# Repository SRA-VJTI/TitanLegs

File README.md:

# TitanLegs

## Schematics

## PCB Design
### Front Side

### Back Side

### Routing

## TASKS

- [ ] Simulation
  - [ ] Plain Terrain
  - [ ] Rough Terrain
- [ ] Design Actuators
  - [ ] SolidWorks Designing
  - [ ] 3D printing of Legs
  - [ ] Assembling the parts
- [ ] Schematics 
- [ ] Firmware
  - [ ] Actuator
  - [ ] Complete Quadruped

## RESOURCES
* [3D Printed Robot Actuator(hackaday project)](https://hackaday.io/project/157812-3d-printed-robot-actuator)
* [GoGo RC Motor(used in above hackaday project)](https://gogo-rc.com/store/index.php?route=product/product&product_id=3493&search=5010)
* [BLDC Motor Algorithm](https://www.renesas.com/us/en/application/home-building/motor-control-solutions/motor-algorithms/bldc)
* [Python Dynamics Simulation-Part 1](https://medium.com/robotics-devs/python-dynamics-simulations-part-1-f89648a35561)
* [Python BLDC Simulator](https://github.com/gtoonstra/bldc-sim)
* [Gait Analysis of Quadruped](https://cjme.springeropen.com/articles/10.1186/s10033-019-0321-2)
* [Brushless Actuator(Arduino Compatible)](https://hackaday.io/project/165217-brushless-actuator-arduino-compatible)
* [ESP-32 BLDC Robot Actuator Controller](https://hackaday.io/project/169905-esp-32-bldc-robot-actuator-controller)
* [Open Source Motor Control - Odrive](https://odriverobotics.com/)
* [Dynamixel- All in one smart Actuator System](https://www.robotis.us/dynamixel/)
* [Quadruped Simulation on Vrep](http://galvanicloop.com/blog/post/7/quadruped-robot-5-simulation-on-v-rep)
* [Quadruped Robots URDF and Simulation tools](https://github.com/chvmp/champ)
* [Fusion 360 script to export URDF](https://github.com/syuntoku14/fusion2urdf)
* [Another Fusion 360 script to export urdf files](https://github.com/yanshil/Fusion2PyBullet)
* [Onshape- browser based CAD tool](https://onshape-to-robot.readthedocs.io/en/latest/design.html)

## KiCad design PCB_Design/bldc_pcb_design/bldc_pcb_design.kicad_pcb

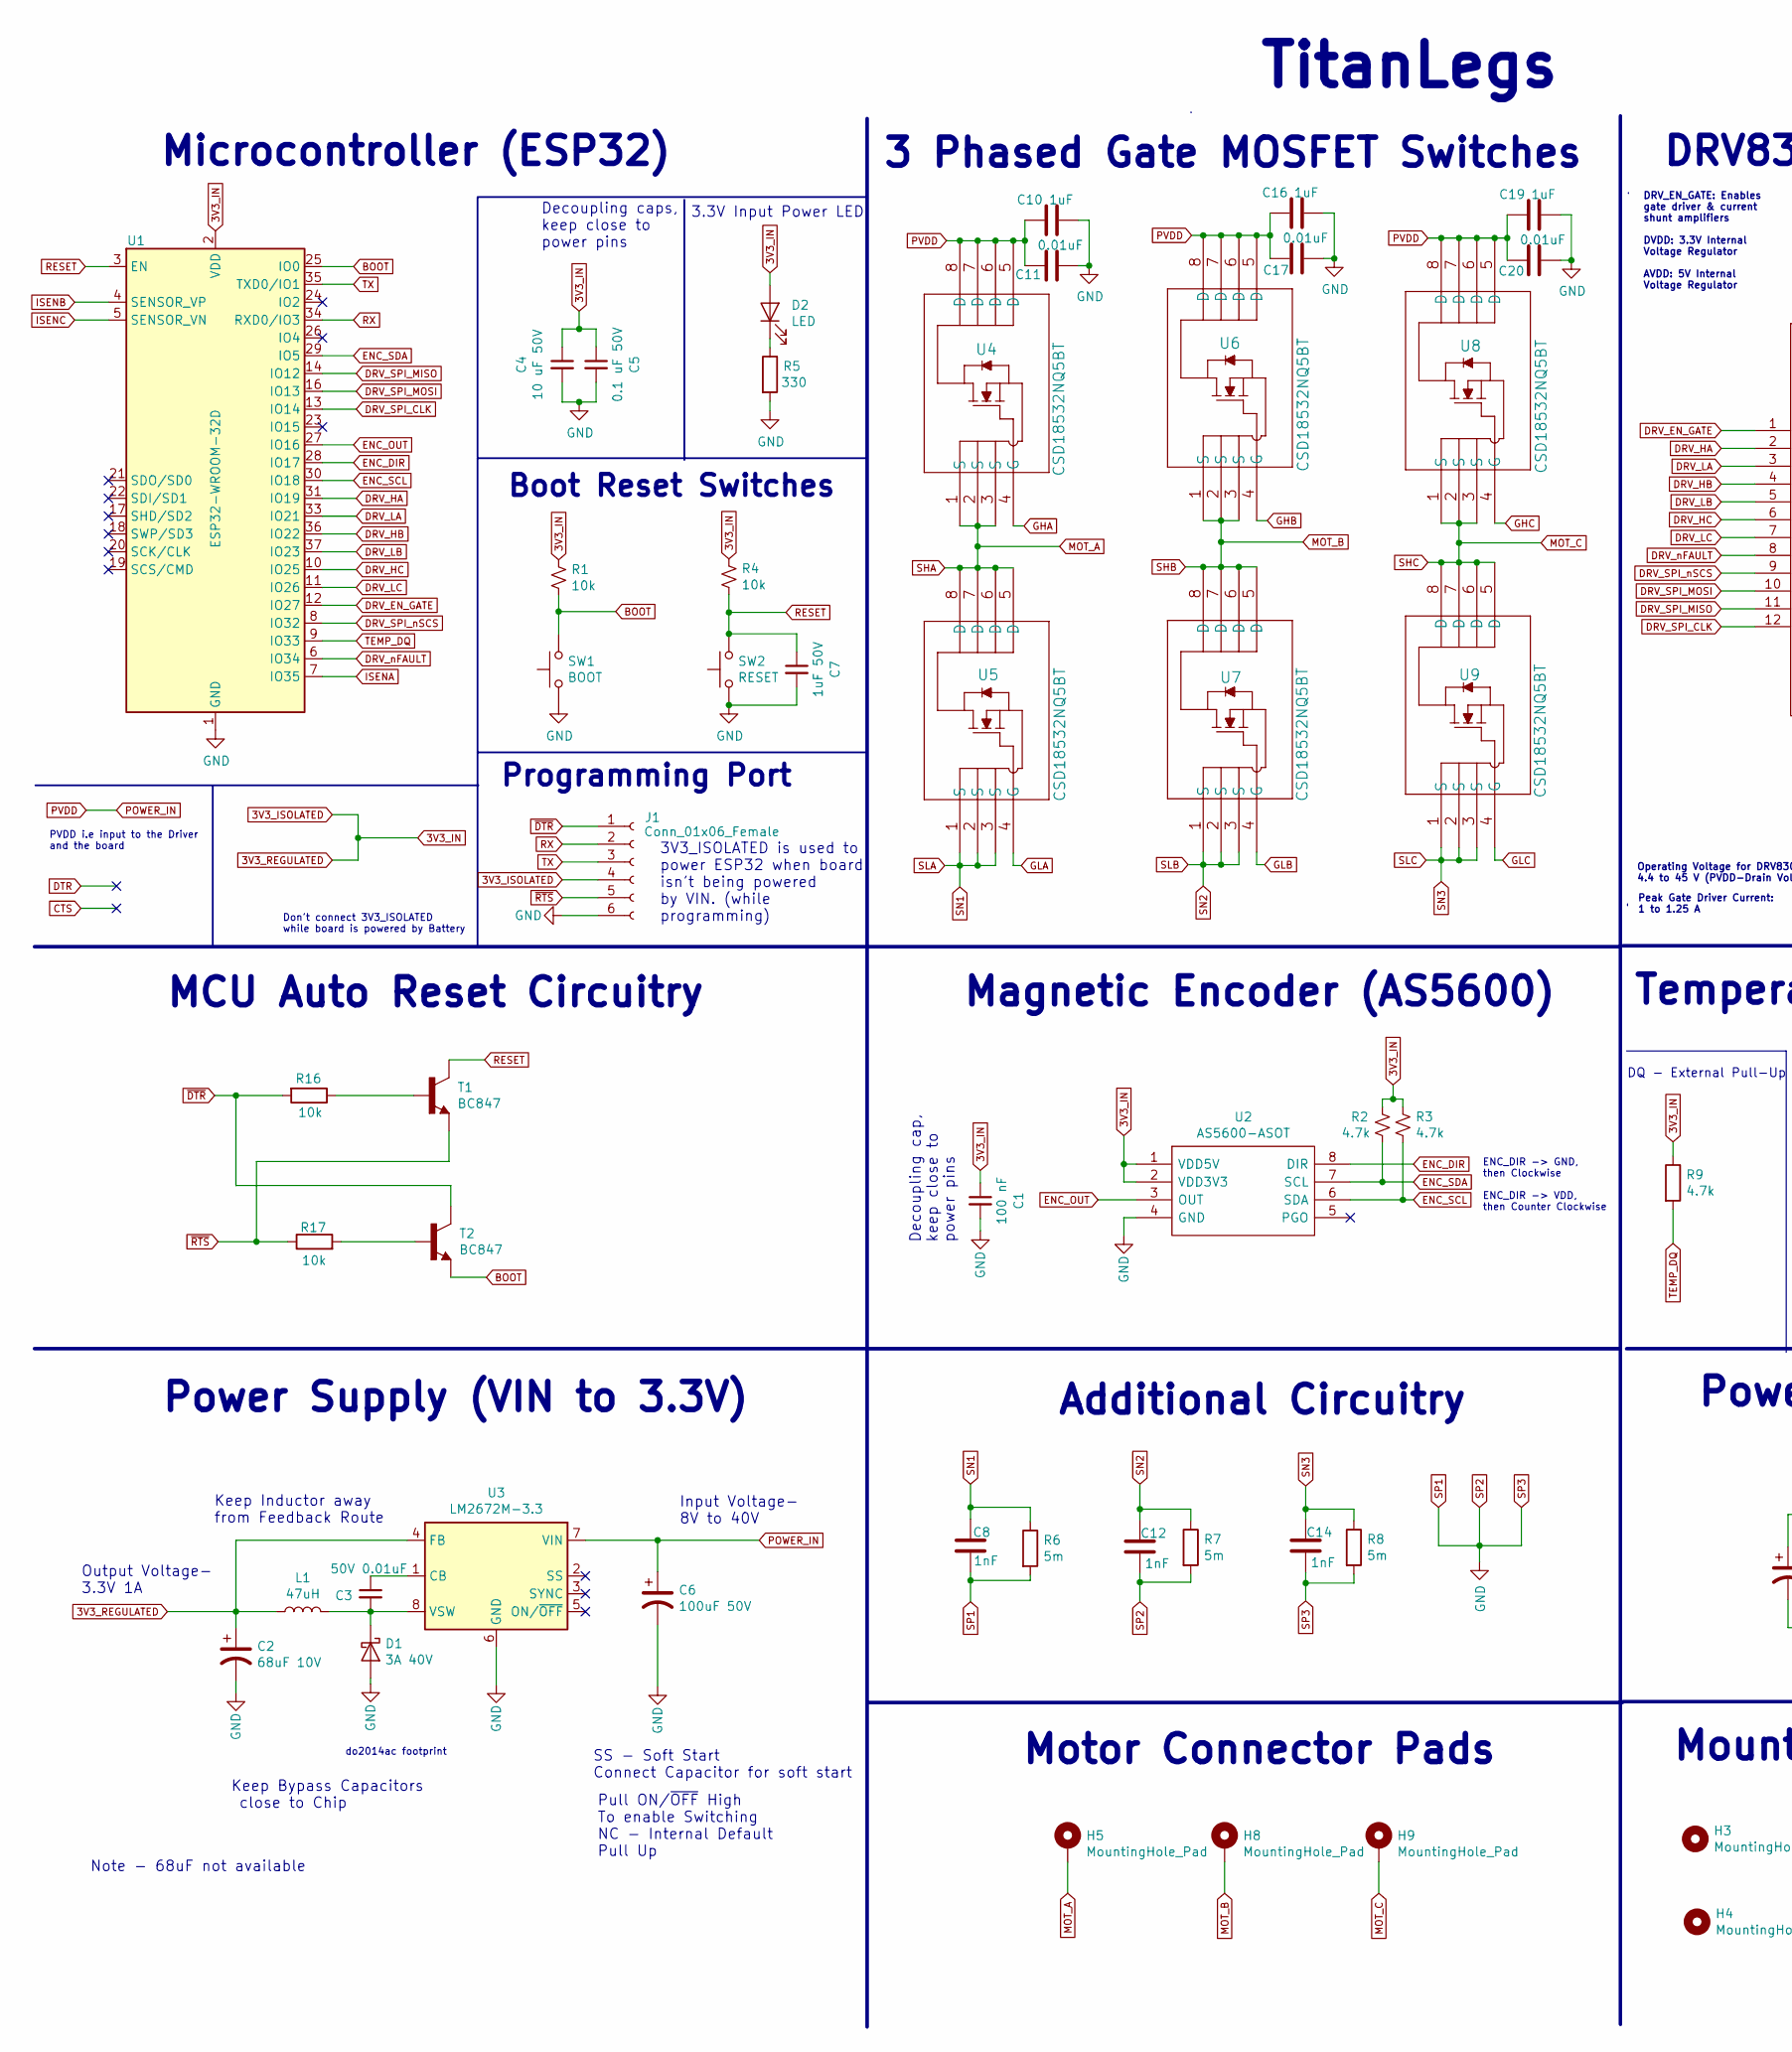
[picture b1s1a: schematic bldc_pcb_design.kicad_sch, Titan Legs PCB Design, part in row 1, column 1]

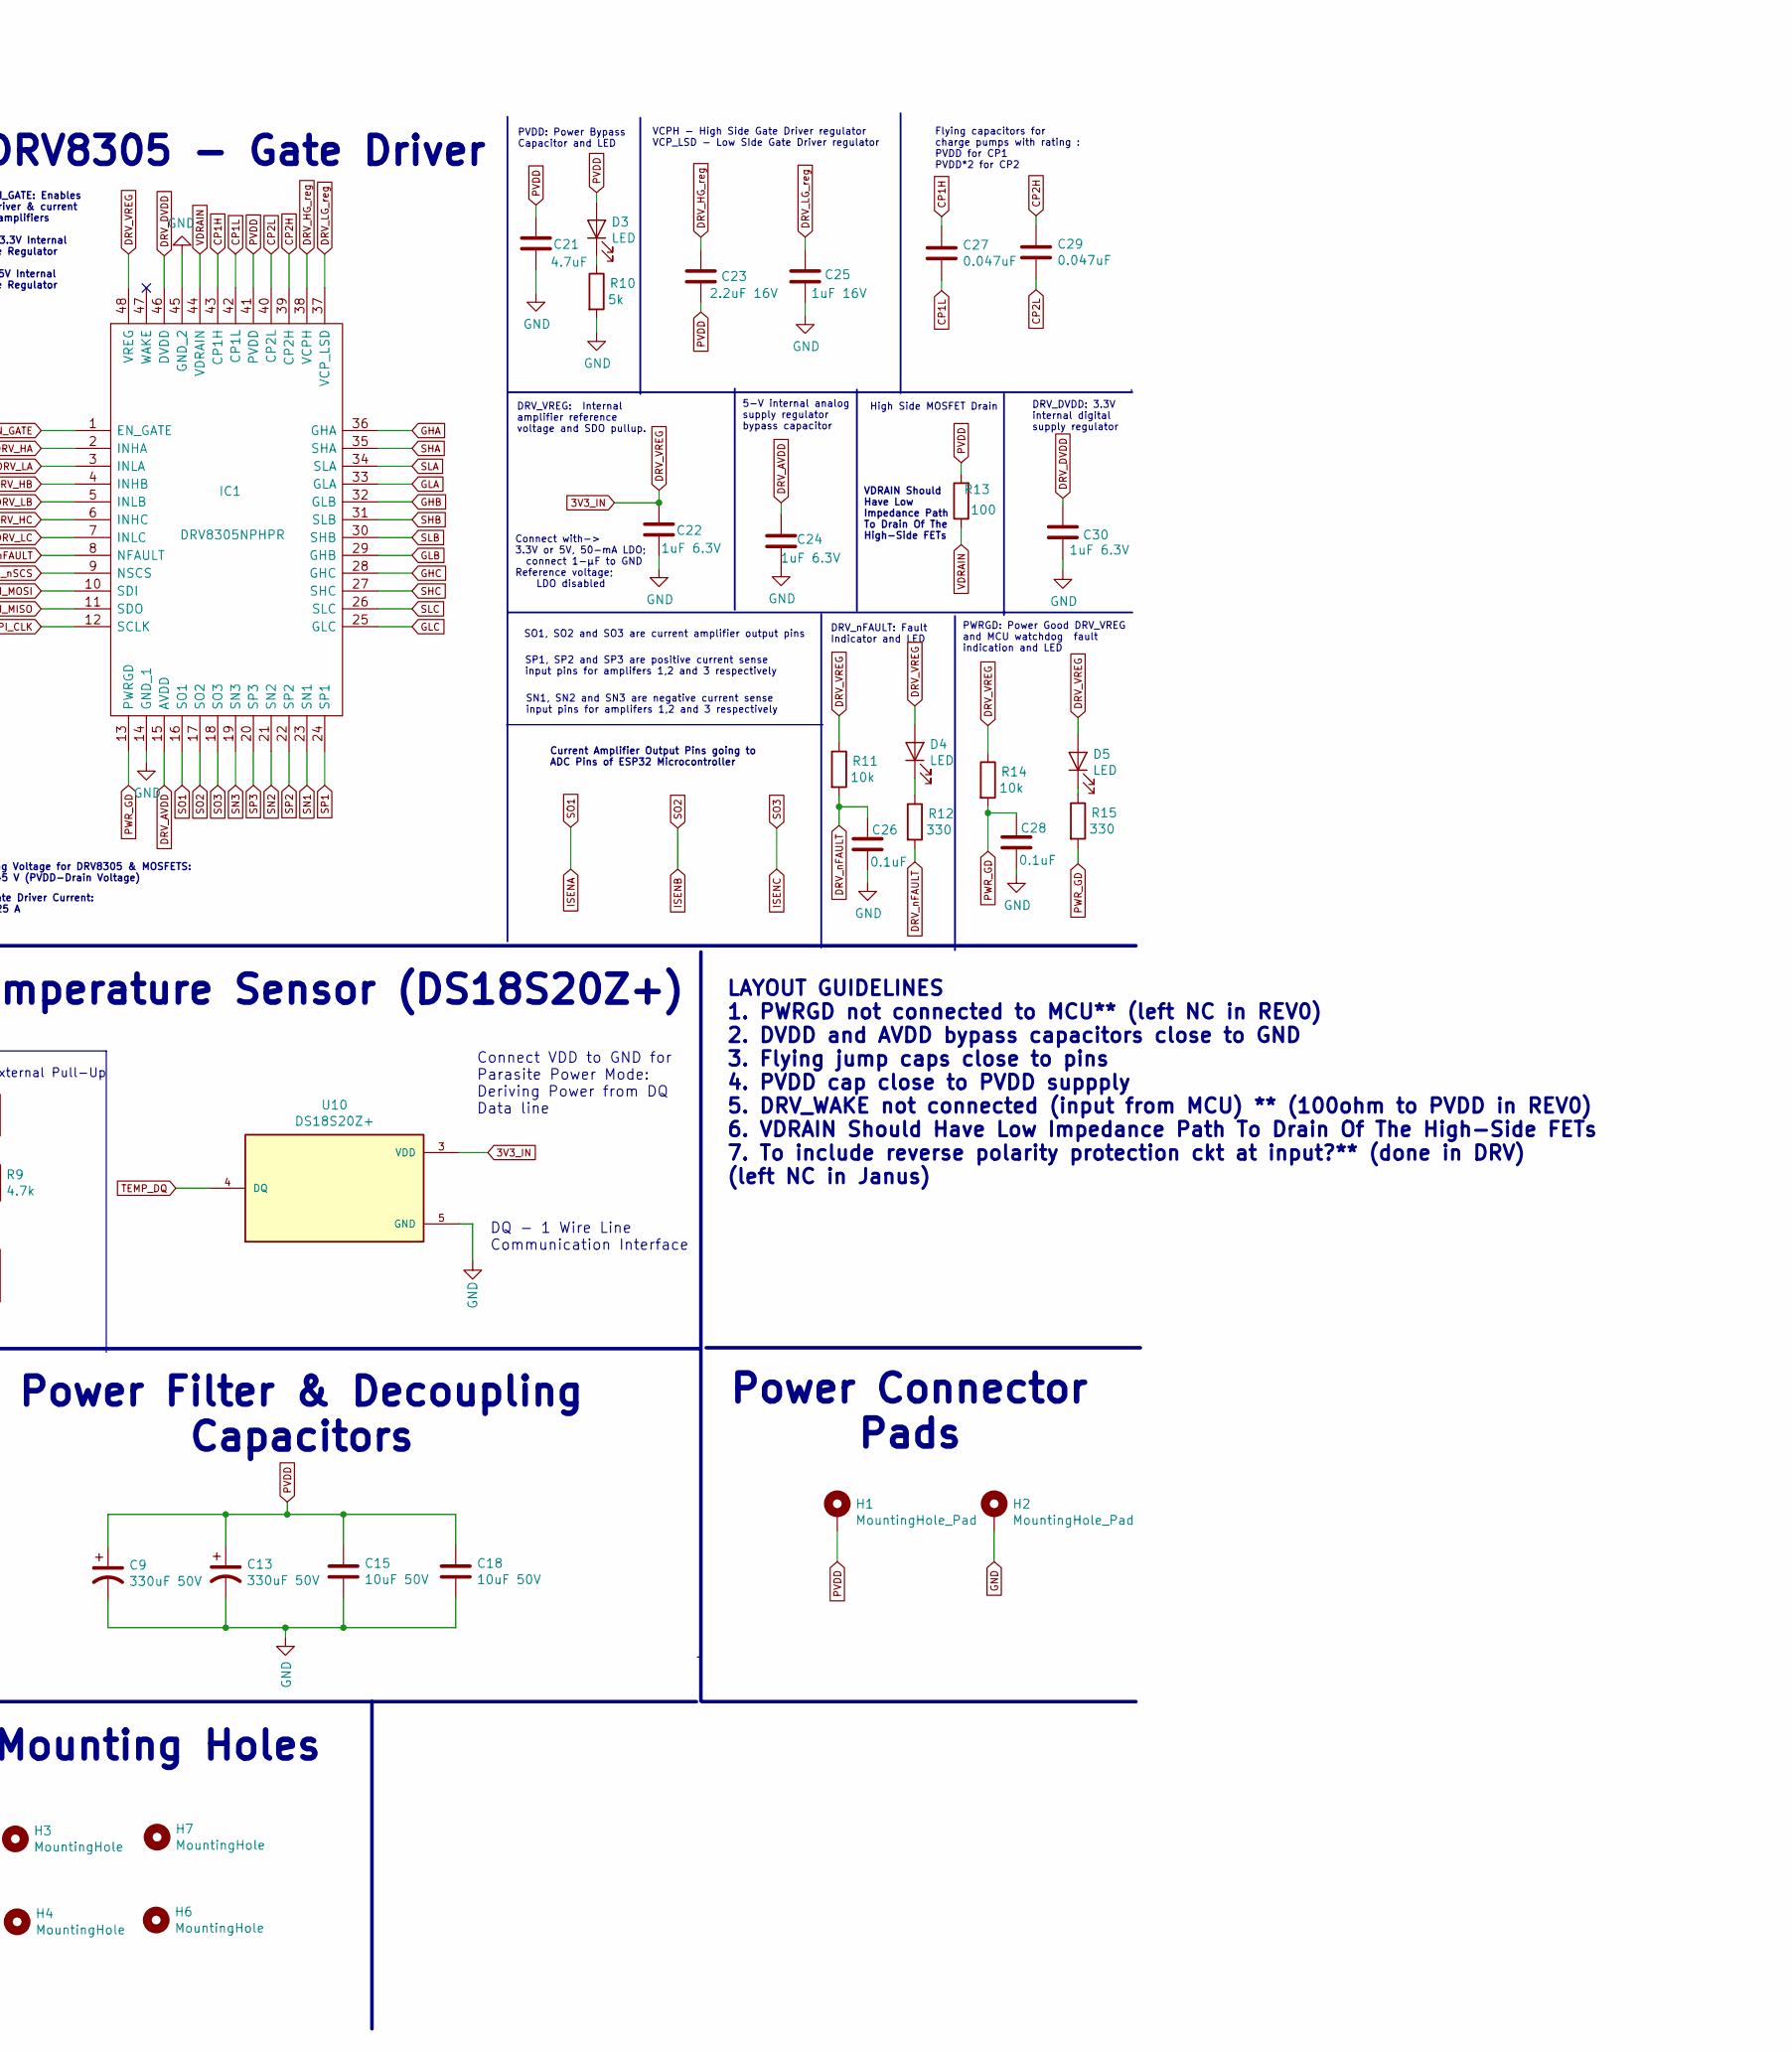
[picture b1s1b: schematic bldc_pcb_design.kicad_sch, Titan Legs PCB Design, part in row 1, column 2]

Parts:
C1: 100 nF; C_0603_1608Metric
C2: 68uF 10V; CP_Elec_6.3x7.7
C3: 50V 0.01uF; C_0603_1608Metric
C4: 10 uF 50V; C_0603_1608Metric
C5: 0.1 uF 50V; C_0603_1608Metric
C6: 100uF 50V; CP_Elec_6.3x7.7
C7: 1uF 50V; C_0603_1608Metric
C8, C12, C14: 1nF; C_0603_1608Metric
C9, C13: 330uF 50V; CP_Elec_10x10
C10, C16, C19: 1uF; C_0603_1608Metric
C11, C17, C20: 0.01uF; C_0603_1608Metric
C15, C18: 10uF 50V; C_0603_1608Metric
C21: 4.7uF; C_0603_1608Metric
C22, C24, C30: 1uF 6.3V; C_0603_1608Metric
C23: 2.2uF 16V; C_0603_1608Metric
C25: 1uF 16V; C_0603_1608Metric
C26, C28: 0.1uF; C_0603_1608Metric
C27, C29: 0.047uF; C_0603_1608Metric
D1: 3A 40V; D_0603_1608Metric
D2, D3, D4, D5: LED; D_0603_1608Metric
H1, H2: MountingHole_Pad; MountingHole_6.4mm_M6_DIN965_Pad
H3, H4, H6, H7: MountingHole; MountingHole_3.2mm_M3
H5, H8, H9: MountingHole_Pad; MountingHole_2.2mm_M2_DIN965_Pad
IC1: DRV8305NPHPR; DRV8305NEPHPRQ1_with_GND_pads; Manufacturer_Part_Number DRV8305NPHPR; Mouser Part Number 595-DRV8305NPHPR
J1: Conn_01x06_Female; PinHeader_1x06_P2.54mm_Vertical
L1: 47uH; 8D43
R1, R4, R11, R14, R16, R17: 10k; R_0603_1608Metric
R2, R3, R9: 4.7k; R_0603_1608Metric
R5, R12, R15: 330; R_0603_1608Metric
R6, R7, R8: 5m; Shunt_Resistor_L7.0mm_B4.0mm_H1.0mm
R10: 5k; R_0603_1608Metric
R13: 100; R_0603_1608Metric
SW1: BOOT; Tactile_Switch
SW2: RESET; Tactile_Switch
T1, T2: BC847
U1: ESP32-WROOM-32D; ESP32-WROOM-32
U2: AS5600-ASOT; AS5600; Manufacturer_Part_Number AS5600-ASOT; Mouser Part Number 985-AS5600-ASOT
U3: LM2672M-3.3; SOIC-8_3.9x4.9mm_P1.27mm
U4, U5, U6, U7, U8, U9: CSD18532NQ5BT; CSD18532NQ5B
U10: DS18S20Z+; DS18S20Z_; PARTREV 3

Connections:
3V3_IN: C1.1, C2.1, C4.1, C5.1, C22.2, D2.2 (A), D4.2 (A), D5.2 (A), IC1.48 (VREG), J1.4, L1.1, R1.1, R2.2, R3.1, R4.1, R9.1, R11.1, R14.1, U1.2 (VDD), U2.1 (VDD5V), U2.2 (VDD3V3), U3.4 (FB), U10.3 (VDD)
BOOT: R1.2, SW1.2, T2.2, U1.25 (IO0)
CP1H: C27.1, IC1.43 (CP1H)
CP1L: C27.2, IC1.42 (CP1L)
CP2H: C29.1, IC1.39 (CP2H)
CP2L: C29.2, IC1.40 (CP2L)
DRV_AVDD: C24.2, IC1.15 (AVDD)
DRV_DVDD: C30.2, IC1.46 (DVDD)
DRV_EN_GATE: IC1.1 (EN_GATE), U1.12 (IO27)
DRV_HA: IC1.2 (INHA), U1.31 (IO19)
DRV_HB: IC1.4 (INHB), U1.36 (IO22)
DRV_HC: IC1.6 (INHC), U1.10 (IO25)
DRV_HG_reg: C23.1, IC1.38 (VCPH)
DRV_LA: IC1.3 (INLA), U1.33 (IO21)
DRV_LB: IC1.5 (INLB), U1.37 (IO23)
DRV_LC: IC1.7 (INLC), U1.11 (IO26)
DRV_LG_reg: C25.1, IC1.37 (VCP_LSD)
DRV_SPI_CLK: IC1.12 (SCLK), U1.13 (IO14)
DRV_SPI_MISO: IC1.11 (SDO), U1.14 (IO12)
DRV_SPI_MOSI: IC1.10 (SDI), U1.16 (IO13)
DRV_SPI_nSCS: IC1.9 (NSCS), U1.8 (IO32)
DRV_nFAULT: C26.1, IC1.8 (NFAULT), R11.2, R12.2, U1.6 (IO34)
ENC_DIR: U1.28 (IO17), U2.8 (DIR)
ENC_OUT: U1.27 (IO16), U2.3 (OUT)
ENC_SCL: R3.2, U1.30 (IO18), U2.6 (SDA)
ENC_SDA: R2.1, U1.29 (IO5), U2.7 (SCL)
GHA: IC1.36 (GHA), U4.4 (G)
GHB: IC1.32 (GLB), U6.4 (G)
GHC: IC1.28 (GHC), U8.4 (G)
GLA: IC1.33 (GLA), U5.4 (G)
GLB: IC1.29 (GHB), U7.4 (G)
GLC: IC1.25 (GLC), U9.4 (G)
GND: C1.2, C2.2, C4.2, C5.2, C6.2, C7.2, C8.2, C9.2, C10.2, C11.2, C12.2, C13.2, C14.2, C15.2, C16.2, C17.2, C18.2, C19.2, C20.2, C21.1, C22.1, C24.1, C25.2, C26.2, C28.2, C30.1, D1.2 (A), H2.1, IC1.14 (GND_1), IC1.20 (SP3), IC1.22 (SP2), IC1.24 (SP1), IC1.45 (GND_2), J1.6, R5.2, R6.2, R7.2, R8.2, R10.2, SW1.1, SW2.1, U1.1 (GND), U1.15 (GND), U1.38 (GND), U1.39 (GND), U2.4 (GND), U3.6 (GND), U10.5 (GND)
ISENA: IC1.16 (SO1), U1.7 (IO35)
ISENB: IC1.17 (SO2), U1.4 (SENSOR_VP)
ISENC: IC1.18 (SO3), U1.5 (SENSOR_VN)
MOT_A: H5.1, IC1.35 (SHA), U4.1 (S), U4.2 (S), U4.3 (S), U5.5 (D), U5.6 (D), U5.7 (D), U5.8 (D)
MOT_B: H8.1, IC1.31 (SLB), U6.1 (S), U6.2 (S), U6.3 (S), U7.5 (D), U7.6 (D), U7.7 (D), U7.8 (D)
MOT_C: H9.1, IC1.27 (SHC), U8.1 (S), U8.2 (S), U8.3 (S), U9.5 (D), U9.6 (D), U9.7 (D), U9.8 (D)
unnamed: C3.1, U3.1 (CB)
unnamed: C3.2, D1.1 (K), L1.2, U3.8 (VSW)
unnamed: D2.1 (K), R5.1
unnamed: D3.1 (K), R10.1
unnamed: D4.1 (K), R12.1
unnamed: D5.1 (K), R15.1
unnamed: R16.1, T1.1
unnamed: R17.2, T2.1
POWER_IN: C6.1, C9.1, C10.1, C11.1, C13.1, C15.1, C16.1, C17.1, C18.1, C19.1, C20.1, C21.2, C23.2, D3.2 (A), H1.1, IC1.41 (PVDD), R13.2, U3.7 (VIN), U4.5 (D), U4.6 (D), U4.7 (D), U4.8 (D), U6.5 (D), U6.6 (D), U6.7 (D), U6.8 (D), U8.5 (D), U8.6 (D), U8.7 (D), U8.8 (D)
PWR_GD: C28.1, IC1.13 (PWRGD), R14.2, R15.2
RESET: C7.1, R4.2, SW2.2, T1.3, U1.3 (EN)
RX: J1.2, U1.34 (RXD0/IO3)
SLA: C8.1, IC1.23 (SN1), IC1.34 (SLA), R6.1, U5.1 (S), U5.2 (S), U5.3 (S)
SLB: C12.1, IC1.21 (SN2), IC1.30 (SHB), R7.1, U7.1 (S), U7.2 (S), U7.3 (S)
SLC: C14.1, IC1.19 (SN3), IC1.26 (SLC), R8.1, U9.1 (S), U9.2 (S), U9.3 (S)
TEMP_DQ: R9.2, U1.9 (IO33), U10.4 (DQ)
TX: J1.3, U1.35 (TXD0/IO1)
VDRAIN: IC1.44 (VDRAIN), R13.1
~DTR: J1.1, R16.2, T2.3
~RTS: J1.5, R17.1, T1.2

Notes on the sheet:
ENC_DIR -> GND, then Clockwise ENC_DIR -> VDD, then Counter Clockwise
Power Connector Pads
Programming Port
DQ - 1 Wire Line Communication Interface
5-V internal analog supply regulator bypass capacitor
Output Voltage- 3.3V 1A
do2014ac footprint
PWRGD: Power Good DRV_VREG and MCU watchdog fault indication and LED
DRV_DVDD: 3.3V internal digital supply regulator
DQ - External Pull-Up
Peak Gate Driver Current: 1 to 1.25 A
LAYOUT GUIDELINES 1. PWRGD not connected to MCU** (left NC in REV0) 2. DVDD and AVDD bypass capacitors close to GND 3. Flying jump caps close to pins 4. PVDD cap close to PVDD suppply 5. DRV_WAKE not connected (input from MCU) ** (100ohm to PVDD in REV0) 6. VDRAIN Should Have Low Impedance Path To 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
Note - 68uF not available
SN1, SN2 and SN3 are negative current sense input pins for amplifers 1,2 and 3 respectively
Operating Voltage for DRV8305 & MOSFETS: 4.4 to 45 V (PVDD-Drain Voltage)
SS - Soft Start Connect Capacitor for soft start
Additional Circuitry
SO1, SO2 and SO3 are current amplifier output pins
Current Amplifier Output Pins going to ADC Pins of ESP32 Microcontroller
Don't connect 3V3_ISOLATED while board is powered by Battery
3V3_ISOLATED is used to power ESP32 when board isn't being powered by VIN. (while programming)
DRV_VREG: Internal amplifier reference voltage and SDO pullup.
High Side MOSFET Drain
Connect VDD to GND for Parasite Power Mode: Deriving Power from DQ Data line
Power Supply (VIN to 3.3V)
Temperature Sensor (DS18S20Z+)
SP1, SP2 and SP3 are positive current sense input pins for amplifers 1,2 and 3 respectively
VDRAIN Should Have Low Impedance Path To Drain Of The High-Side FETs
Boot Reset Switches
DRV_EN_GATE: Enables gate driver & current shunt amplifiers DVDD: 3.3V Internal Voltage Regulator AVDD: 5V Internal Voltage Regulator
DRV_nFAULT: Fault Indicator and LED
Pull ON/~{OFF} High To enable Switching NC - Internal Default Pull Up
Flying capacitors for charge pumps with rating : PVDD for CP1 PVDD*2 for CP2
Microcontroller (ESP32)
Keep Bypass Capacitors close to Chip
Mounting Holes
PVDD i.e input to the Driver and the board
TitanLegs
Decoupling cap, keep close to power pins
VCPH - High Side Gate Driver regulator VCP_LSD - Low SIde Gate Driver regulator

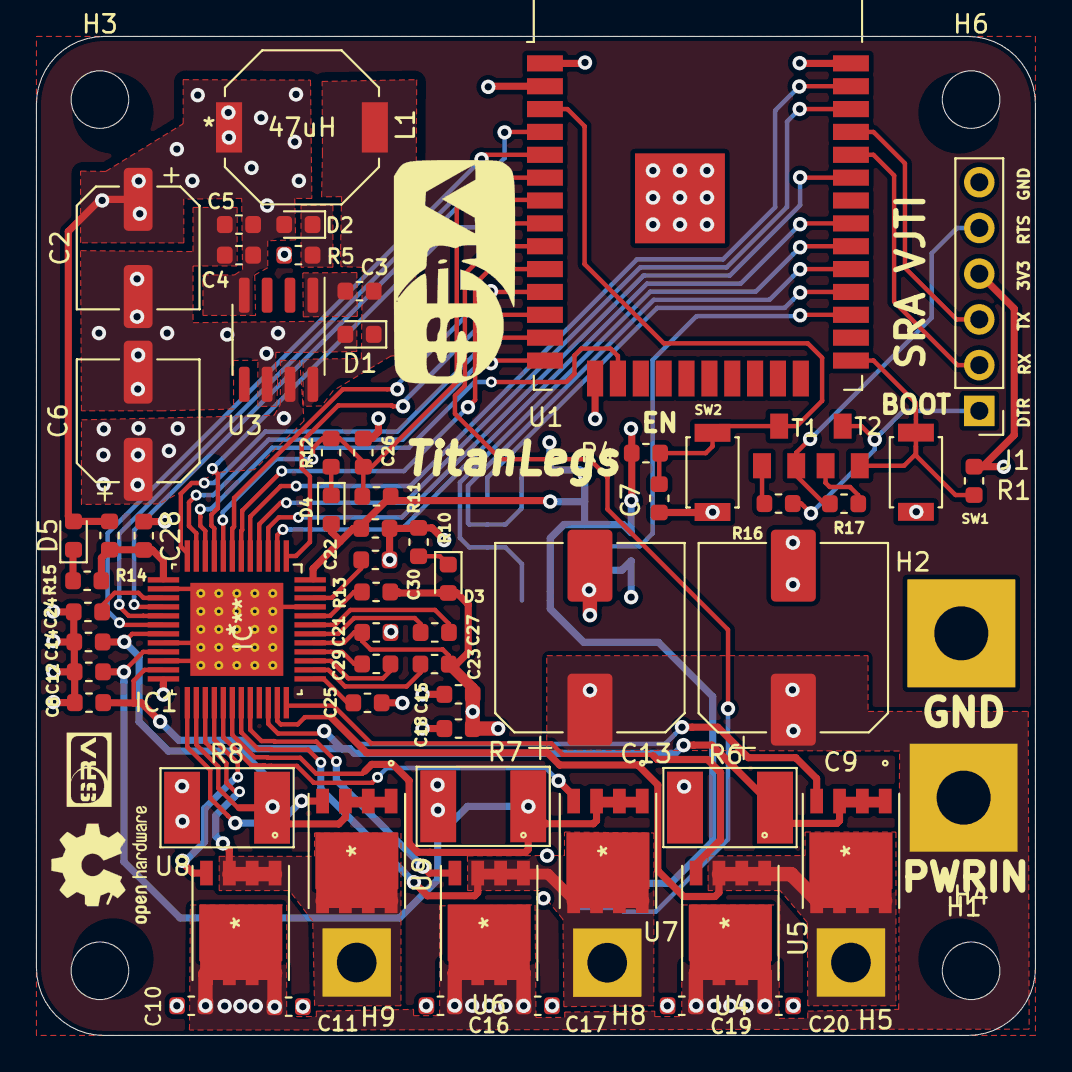
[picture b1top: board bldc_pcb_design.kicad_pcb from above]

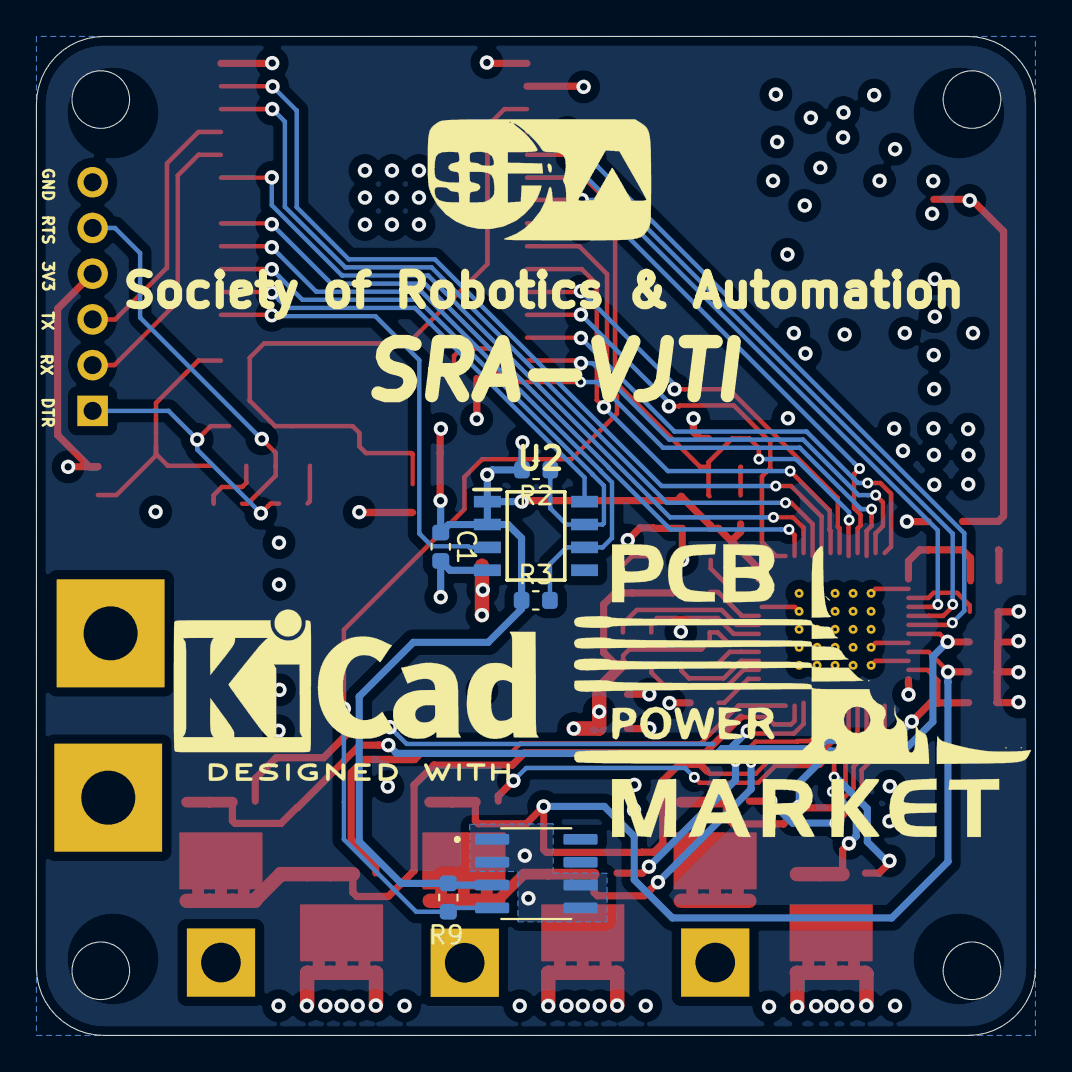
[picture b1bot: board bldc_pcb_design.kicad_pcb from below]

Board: 4 copper layers, 55.5 x 55.5 mm, 78 parts (6 on the bottom side), 59 nets.

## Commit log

2021-06-21 Added Resources to Readme
2021-06-23 Mechanical Design
2021-06-23 Revert "Mechanical Design"
    This reverts commit 3625ce9c8420bc28083b0ad78ce3180cb9b17e8c.
2021-06-23 Assets
2021-06-23 Design changes
2021-06-24 Updates in Gearbox Design (#1)
    * Mechanical Design
    * Revert "Mechanical Design"
    This reverts commit 3625ce9c8420bc28083b0ad78ce3180cb9b17e8c.
    * Assets
    * Create README.md
    * Update README.md
2021-07-31 Added PCB schematics, assets and datasheets
2021-07-31 Minor fix-2
2021-07-31 Added PCB schematics, assets and datasheets-2
2021-07-31 Updated .gitignore file
2021-07-31 Removed redundant files
2021-08-23 Started schematics design from scratch
2021-08-23 Completed schematics of ESP32 and Encoder
2021-09-02 WIP: Added Switching mode regulator schematics
2021-09-02 Added component values for buck converter
2021-09-02 Backlink to CADLAB.io has been added.
2021-09-05 Buggy Code commit
2021-09-05 Added example as temporary main code
2021-09-05 Added esp32-drv8305-driver as submodule
2021-09-05 Removed old files and added README
2021-09-05 DRV8305 EN gate pin defined
    No output yet
2021-09-05 Works for now (No runtime errors)
    However reading from 0x5 should give 3 but it's displaying 0
    Referred SPI config from https://github.com/espressif/esp-idf/issues/3337
2021-09-05 Added Skeleton for the DRV8305 Driver
2021-09-05 Vscode gitignore
    Added vscode gitignore
    Added sdkconfigs
2021-09-07 Added schematics for DRV8305
2021-09-07 Added TI Mosfets and LEDS
2021-09-08 Modified GPIO connections
2021-09-15 [Temp sensor] Added DS18S20Z+ and modified schematics
2021-09-28 Changed pin connections: IO34- DRV_nFAULT; IO15- NC; IO33- TEMP_DQ
2021-10-04 Optimised Schematics
2021-10-07 Added Motor connector pads, rectified connections
2021-10-27 Annotated components and assigned footprints
2021-11-09 Replaced Xt connector with motor pads
2021-11-09 Added Leg Design
2021-11-09 Added GearBox STLs
2021-11-11 Rough placement of components done for Routing. PCB Diameter : 78mm Circular
2021-11-11 Generated bldc_pcb_design.net Netlist file
2021-11-11 Modified Part Tolerances
2022-01-05 Routing Iteration 1 done, Rectified schematics (SOx and shunt resistor connections)
2022-01-11 Made routing changes and optimized schematics, pcbnew
2022-01-11 Minor Silkscreen changes
2022-01-14 Routed buck converter LM2672 by copper fills - FCu
2022-01-20 Re-routed DRV8305 using corrected underneath GND pad footprint, back mounted Temp sensor
2022-01-20 Assigned common GND net to DRV8305's Central GND pad - PTH Holed Vias
2022-01-21 Temp Sensor - Modified BCu Exposed Cu, B.Paste for better alignment
2022-01-21 [FIX] Modified .gitgnore
    * Previously .gitignore had submodules
2022-01-21 Add driver for as5600
2022-01-21 Modified SilkScreen
2022-01-22 Add API for setting the max angle in AS5600
2022-01-22 Solve a syntax error

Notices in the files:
PCB_Design/bldc_pcb_design/bldc_pcb_design.kicad_sch:
MIT License
parts and their libraries:
Copyright 2021 Accelerated Designs. All rights reserved.
